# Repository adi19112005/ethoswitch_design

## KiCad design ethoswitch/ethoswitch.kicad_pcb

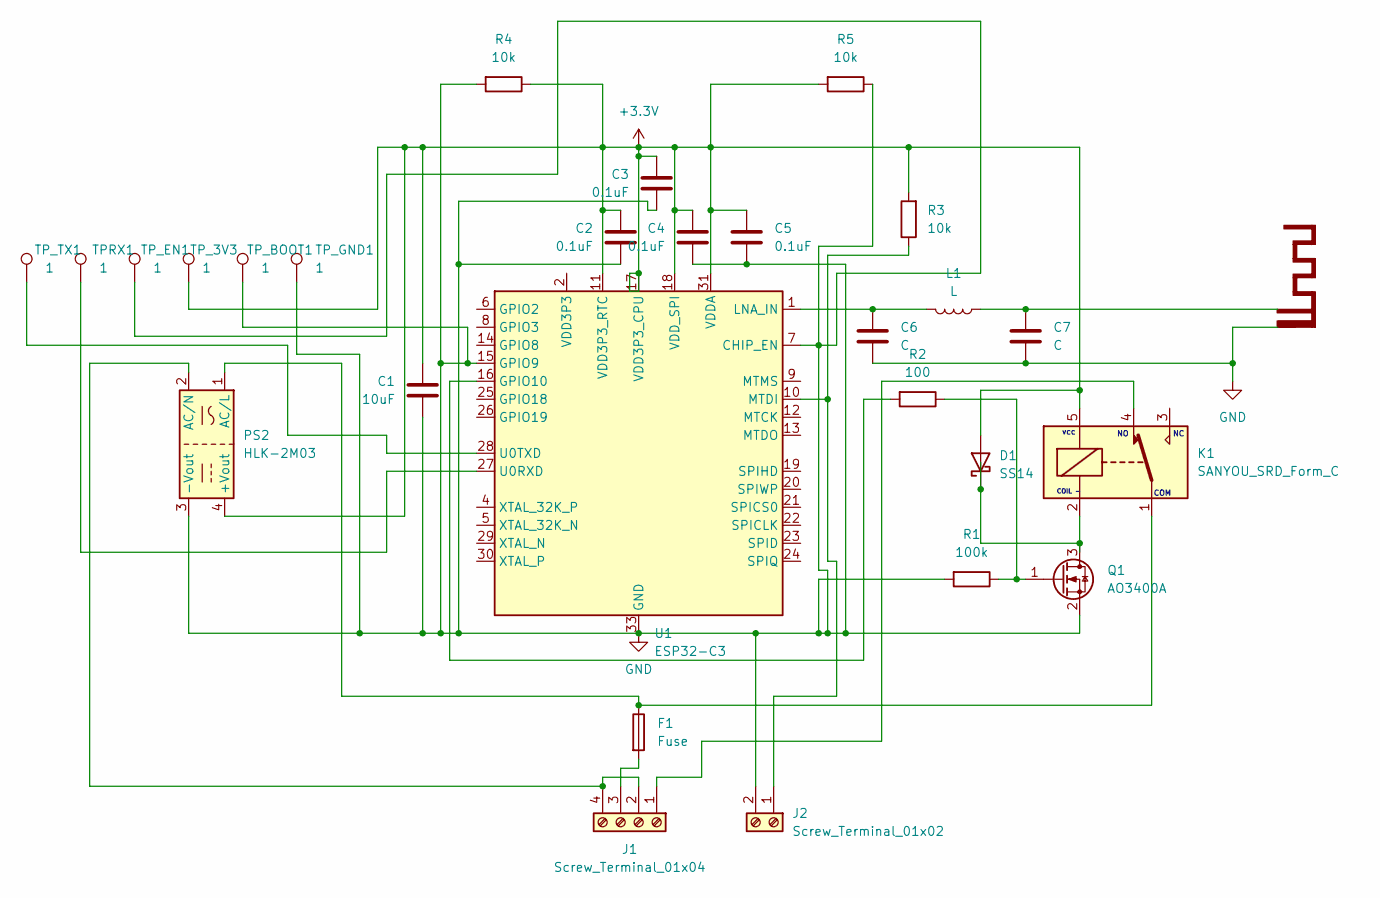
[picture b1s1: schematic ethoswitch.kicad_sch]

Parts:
AE2: Antenna; Texas_SWRA117D_2.4GHz_Left
C1: 10uF; C_0805_2012Metric
C2, C3, C4, C5: 0.1uF; C_0603_1608Metric
C6, C7: C; C_0603_1608Metric
D1: SS14; D_SMA
F1: Fuse; Fuse_0603_1608Metric
J1: Screw_Terminal_01x04; TerminalBlock_Phoenix_MPT-0,5-4-2.54_1x04_P2.54mm_Horizontal
J2: Screw_Terminal_01x02; TerminalBlock_Phoenix_MPT-0,5-2-2.54_1x02_P2.54mm_Horizontal
K1: SANYOU_SRD_Form_C; Relay_SPDT_SANYOU_SRD_Series_Form_C
L1: L; L_0805_2012Metric
PS2: HLK-2M03; Converter_ACDC_Hi-Link_HLK-2Mxx
Q1: AO3400A; SOT-23
R1: 100k; R_0603_1608Metric
R2: 100; R_0603_1608Metric
R3, R4, R5: 10k; R_0603_1608Metric
TPRX1: 1; TestPoint_Pad_D1.0mm
TP_3V3: 1; TestPoint_Pad_D1.0mm
TP_BOOT1: 1; TestPoint_Pad_D1.0mm
TP_EN1: 1; TestPoint_Pad_D1.0mm
TP_GND1: 1; TestPoint_Pad_D1.0mm
TP_TX1: 1; TestPoint_Pad_D1.0mm
U1: ESP32-C3; QFN-32-1EP_5x5mm_P0.5mm_EP3.7x3.7mm

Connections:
+3.3V: C1.1, C2.1, C3.1, C4.1, C5.1, D1.2 (A), K1.5, PS2.4 (+Vout), R3.2, R4.1, R5.2, TP_3V3.1, U1.11 (VDD3P3_RTC), U1.17 (VDD3P3_CPU), U1.18 (VDD_SPI), U1.31 (VDDA), U1.32 (VDDA)
GND: AE2.1 (A), C1.2, C2.2, C3.2, C4.2, C5.2, C6.2, C7.2, J2.2, PS2.3 (-Vout), Q1.2 (S), R1.2, R4.2, R5.1, TP_BOOT1.1, TP_EN1.1, TP_GND1.1, U1.7 (CHIP_EN), U1.15 (GPIO9), U1.33 (GND)
unnamed: C7.1, L1.1
unnamed: D1.1 (K), K1.2, Q1.3 (D)
unnamed: J1.1, K1.4
unnamed: J1.2, J1.4, PS2.2 (AC/N)
unnamed: F1.2, J1.3
unnamed: J2.1, R3.1, U1.10 (MTDI)
unnamed: F1.1, K1.1, PS2.1 (AC/L)
unnamed: Q1.1 (G), R1.1, R2.1
unnamed: R2.2, U1.16 (GPIO10)
unnamed: C6.1, L1.2, U1.1 (LNA_IN)
unnamed: TPRX1.1, U1.27 (U0RXD)
unnamed: TP_TX1.1, U1.28 (U0TXD)
unnamed: U1.2 (VDD3P3), U1.3 (VDD3P3)

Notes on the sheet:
vcc
COIL -
COM

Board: 2 copper layers, 28 parts (0 on the bottom side), 15 nets, no tracks yet.

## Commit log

2026-01-19 Initial Commit
    Only KiCad Files
2026-01-20 PCB File
    Placement
